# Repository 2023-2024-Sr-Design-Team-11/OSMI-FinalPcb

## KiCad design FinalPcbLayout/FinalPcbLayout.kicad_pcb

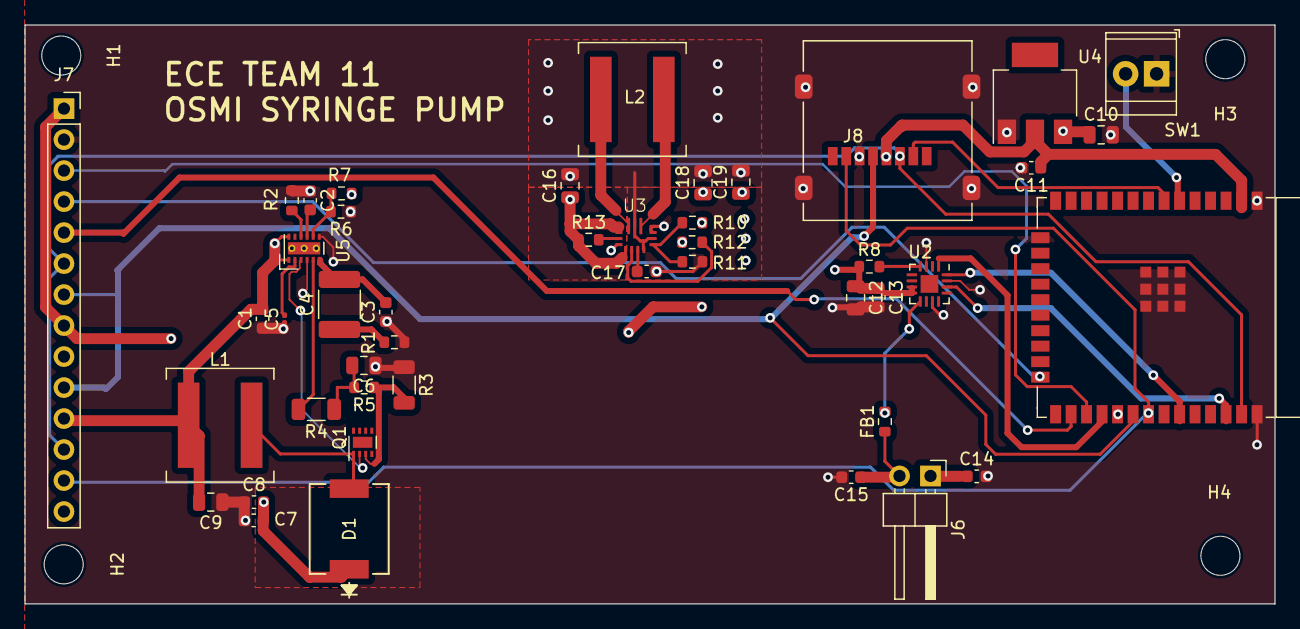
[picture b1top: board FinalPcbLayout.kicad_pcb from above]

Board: 4 copper layers, 102.4 x 47.4 mm, 49 parts (0 on the bottom side), 36 nets.

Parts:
C1, C2, C17: 100nF; C_0603_1608Metric
C3: 6.8nF; C_0603_1608Metric
C4: 15nF; C_1812_4532Metric
C5: 1uF; C_0201_0603Metric
C6: 1nF; C_0805_2012Metric
C7, C11: 22uF; C_0603_1608Metric
C8: 1uF; C_0603_1608Metric
C9, C10, C12, C16, C18: 10uF; C_0805_2012Metric
C13: 0.1uF; C_0603_1608Metric
C14, C15: 220pF; C_0603_1608Metric
C19: 47uF; C_0805_2012Metric
D1: D_Schottky; CR_2-E3&slash_57T_VIS
FB1: FerriteBead; R_0603_1608Metric
H1, H2, H3, H4: MountingHole; MountingHole_3.2mm_M3
J6: Conn_01x02_Pin; PinHeader_1x02_P2.54mm_Horizontal
J7: Display Socket; PinSocket_1x14_P2.54mm_Vertical
J8: Micro_SD_Card; microSD_HC_Molex_47219-2001
L1: 2.2uH; L_Coilcraft_XAL8050-223
L2: L; L_Coilcraft_XAL8050-223
Q1: NMOS; WSON-8-1EP_2x2mm_P0.5mm_EP0.9x1.6mm
R1: 3.3k; R_0603_1608Metric
R2: 21k; R_0603_1608Metric
R3: 12m; R_1206_3216Metric
R4: 487; R_1206_3216Metric
R5: 100; R_0603_1608Metric
R6: 2.49k; R_0603_1608Metric
R7: 27.4; R_0603_1608Metric
R8: 370k; R_0603_1608Metric
R10: 523k; R_0603_1608Metric
R11, R12: 100k; R_0603_1608Metric
R13: 10k; R_0603_1608Metric
SW1: SW_Push; TerminalBlock_TE_282834-2_1x02_P2.54mm_Horizontal
U1: ESP32-WROOM-E; ESP32-WROOM-32E
U2: QFN-16-1EP_3x3mm_P0.5mm_EP1.45x1.45mm
U3: VQFN-15-1EP-2.5x3mm_P0.5mm
U4: AMS1117-3.3; SOT-223
U5: WSON-12-1EP_3x2mm_P0.5mm_EP1x2.65_ThermalVias

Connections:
+3.3V: C11.1, J7.1, J7.8, J8.4 (VDD), U1.2 (3V3), U4.2 (VO)
+5V: C10.1, C12.1, C13.1, C18.1, C19.1, R8.1, R10.1, R12.1, U2.7 (VDD), U2.8 (VDD), U3.7 (VOUT), U3.8 (VOUT), U4.3 (VI)
/CIPO: J7.13, J8.7 (DAT0), U1.31 (GPIO19)
/COPI: J7.6, J7.12, J8.3 (CMD), U1.37 (GPIO23)
/Display_CS: J7.3, U1.27 (GPIO16)
/Display_DC: J7.5, U1.26 (ADC2_CH0/GPIO4)
/Display_RST: J7.4, U1.24 (ADC2_CH2/GPIO2)
/ESTOP: SW1.2, U1.6 (GPIO34/ADC1_CH6)
/IO17: U1.28 (GPIO17), U2.1 (DIN)
/IO21: U1.33 (GPIO21), U2.16 (BCLK)
/IO22: U1.36 (GPIO22), U2.14 (LRCLK)
/Power/V_in: C1.2, C7.2, C8.2, C9.2, C16.1, D1.1 (K), J7.11, L1.1, R7.2, R13.1, U1.29 (GPIO5), U3.1 (PS/SYNC), U3.12 (VIN), U3.13 (VIN), U5.1 (BIAS), U5.12 (UVLO_)
/SCLK: J7.7, J7.10, J8.5 (CLK), U1.30 (GPIO18)
/SD_CS: J8.2 (DAT3/CD), U1.7 (GPIO35/ADC1_CH7)
/SD_MODE: R8.2, U2.4 (SD_MODE)
GND: C1.1, C2.1, C3.1, C5.1, C6.1, C7.1, C8.1, C9.1, C10.2, C11.2, C12.2, C13.2, C14.2, C15.2, C16.2, C17.2, C18.2, C19.2, J7.2, J8.6 (VSS), J8.9 (SHIELD), R1.1, R2.1, R3.1, R6.1, R11.2, SW1.1, U1.1 (GND), U1.15 (GND), U1.38 (GND), U1.39 (GND_THERMAL), U2.3 (GND), U2.11 (GND), U2.15 (GND), U3.4 (GND), U3.6 (FB2), U3.10 (PGND), U3.15 (VSEL), U4.1 (GND), U5.4 (PGND), U5.7 (AGND)
unnamed: C4.1, R1.2
unnamed: C6.2, R4.1, R5.2
unnamed: D1.2 (A), L1.2, Q1.1 (D)
unnamed: C14.1, J6.1
unnamed: C15.1, FB1.1, J6.2
unnamed: Q1.2 (G), U5.3 (GATE)
unnamed: Q1.3 (S), R3.2, R5.1
unnamed: FB1.2, U2.9 (OUTP)
unnamed: R13.2, U3.14 (EN)
unnamed: R10.2, R11.1, U3.5 (FB)
unnamed: L2.1, U3.11 (L1)
unnamed: L2.2, U3.9 (L2)
unnamed: R12.2, U3.2 (PG)
unnamed: C17.1, U3.3 (VAUX)
unnamed: C3.2, C4.2, U5.6 (COMP)
unnamed: R4.2, U5.5 (CS)
unnamed: R6.2, R7.1, U5.8 (FB)
unnamed: R2.2, U5.10 (RT)
unnamed: C2.2, U5.9 (SS)
unnamed: C5.2, U5.2 (VCC)

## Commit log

2024-01-23 tyra's changes
2024-01-23 let's try again
2024-01-24 onelineinthefootprint
2024-01-24 Links and costs
2024-01-24 routing
2024-01-24 Closed the schematic
2024-01-24 some footprint updates
